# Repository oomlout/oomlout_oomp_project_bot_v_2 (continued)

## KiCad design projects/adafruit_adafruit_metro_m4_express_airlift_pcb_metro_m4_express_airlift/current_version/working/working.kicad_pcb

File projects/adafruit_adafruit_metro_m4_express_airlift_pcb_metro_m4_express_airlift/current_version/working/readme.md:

# adafruit_metro_m4_express_airlift_pcb
 
## summary 
* id: adafruit_adafruit_metro_m4_express_airlift_pcb_metro_m4_express_airlift
* user: adafruit
* name: adafruit_metro_m4_express_airlift_pcb
* board: metro_m4_express_airlift
* repo: https://github.com/adafruit/Adafruit-Metro-M4-Express-AirLift-PCB

* src_file_repo_sch: 
* src_file_repo_sch_link: https://github.com/adafruit/Adafruit-Metro-M4-Express-AirLift-PCB/tree/master/
* full details link: https://github.com/oomlout/oomlout_oomp_project_bot_v_2/tree/main/projects/adafruit_adafruit_metro_m4_express_airlift_pcb_metro_m4_express_airlift/current_version/working  

## schematic  
  
[schematic (pdf)](working_schematic.pdf) 

## pcb  

[board (pdf)](working.pdf)  

## working_bom
| Id | Designator | Footprint | Quantity | Designation | Supplier and ref |  | None | 
| --- | --- | --- | --- | --- | --- | --- | --- | 
| 1 | C7,C5 | 0603-NO | 2 | 22pF |  |  | [''] | 
| 2 | U$1 | PQFN64-1 | 1 | ATSAMD51J19 |  |  | [''] | 
| 3 | LED1 | LED3535 | 1 | WS2812B3535 |  |  | [''] | 
| 4 | @HOLE0,@HOLE1,@HOLE3,@HOLE2 |  | 4 |  |  |  | [''] | 
| 5 | C15,C8,C6,C14,C16,C4,C11,C10 | 0603-NO | 8 | .1u |  |  | [''] | 
| 6 | X5 | DCJACK_2MM_PTH | 1 | 2.1mm |  |  | [''] | 
| 7 | SW1 | SPDT_SMT_SSSS811101 | 1 |  |  |  | [''] | 
| 8 | C2 | 0805-NO | 1 | 0.1uF |  |  | [''] | 
| 9 | PC2 | PANASONIC_D | 1 | 47uF+/6.3V+ |  |  | [''] | 
| 10 | ON0 | CHIPLED_0805_NOOUTLINE | 1 | GREEN |  |  | [''] | 
| 11 | C3,C1,C20,C18,C19 | 0805-NO | 5 | 10uF |  |  | [''] | 
| 12 | SJ1 | SOLDERJUMPER_CLOSEDWIRE | 1 | AREF_3V |  |  | [''] | 
| 13 | C12,C13,C17 | 0603-NO | 3 | 0.1uF |  |  | [''] | 
| 14 | IC1 | SOT23-5L | 1 | 74AHC1G125 |  |  | [''] | 
| 15 | TR1,T2 | SOT-23 | 2 | DMP3098L-7 |  |  | [''] | 
| 16 | PC1 | PANASONIC_D | 1 | 47uF/25V |  |  | [''] | 
| 17 | FD2,FD1,FD3 | FIDUCIAL_1MM | 3 | FIDUCIAL_1MM |  |  | [''] | 
| 18 | POWER0,IOL0 | 1X08_OVALWAVE | 2 | 20610 |  |  | [''] | 
| 19 | L1 | INDUCTOR_1007 | 1 | 10uH |  |  | [''] | 
| 20 | R5,R15,R7 | 0603-NO | 3 | 10K |  |  | [''] | 
| 21 | RXLED0,TXLED0 | CHIPLED_0805_NOOUTLINE | 2 | YELLOW |  |  | [''] | 
| 22 | AD0 | 1X06_OVALWAVE | 1 | 20609 |  |  | [''] | 
| 23 | U2 | SOT23-DBV | 1 | AP2112K-3.3 |  |  | [''] | 
| 24 | X2 | 2X05_1.27MM_BOX_POSTS | 1 | 2x5 0.05 SWD" |  |  | [''] | 
| 25 | L0 | CHIPLED_0805_NOOUTLINE | 1 | RED |  |  | [''] | 
| 26 | R11 | 0603-NO | 1 | 330R |  |  | [''] | 
| 27 | U$39 | METROM4_AIRLIFT_LITE_TOP | 1 |  |  |  | [''] | 
| 28 | R1 | RESPACK_4X0603 | 1 | 100K |  |  | [''] | 
| 29 | X6 | WROOM32 | 1 | ESP32_WROOM32 |  |  | [''] | 
| 30 | IOH0 | 1X10_OVALWAVE | 1 | 20611 |  |  | [''] | 
| 31 | JP1 | 1X01_ROUND | 1 |  |  |  | [''] | 
| 32 | R10 | RESPACK_4X0603 | 1 | 10K |  |  | [''] | 
| 33 | ECC1 | SOIC8 | 1 | ATECC108 |  |  | [''] | 
| 34 | C9 | 0603-NO | 1 | 1uF |  |  | [''] | 
| 35 | D1 | SOD-123 | 1 | MBR120 |  |  | [''] | 
| 36 | ICSP0 | 2X03_ROUND_70MIL | 1 | 3x2 M |  |  | [''] | 
| 37 | X4 | XTAL3215 | 1 | 32.768 |  |  | [''] | 
| 38 | U3 | SOIC8_208MIL | 1 | GD25Q16 |  |  | [''] | 
| 39 | X3 | 4UCONN_20329_V2 | 1 | 20329 |  |  | [''] | 
| 40 | IC3 | SOT23-5 | 1 | 74LVC1G125D |  |  | [''] | 
| 41 | U1 | SOT223-R | 1 | NCP1117ST50T3G |  |  | [''] | 
| 42 | R4 | 0603-NO | 1 | 1K |  |  | [''] | 
| 43 | FB2 | 0805-NO | 1 | FERRITE |  |  | [''] | 
| 44 | RESET0 | EVQ-Q2_SMALLER | 1 | EVQQ 6mm |  |  | [''] | 
| 45 | F2 | R1206 | 1 | FUSE |  |  | [''] | 
| 46 | R2 | RESPACK_4X0603 | 1 | 1K |  |  | [''] | 
| 47 | U$27 | METROM4_AIRLIFT_LITE_BOT | 1 |  |  |  | [''] | 
| 48 | GROUND1 | SOLDERJUMPER_CLOSEDWIRE | 1 |  |  |  | [''] | 

## bom_schematic
| Ref | Qnty | Value | Cmp name | Footprint | Description | Vendor | DNP | 
| --- | --- | --- | --- | --- | --- | --- | --- | 
| AD0 | 1 | 20609 | HEADER-1X6OVALWAVE | working:1X06_OVALWAVE |  |  |  | 
| C1, C3, C18, C19, C20 | 5 | 10uF | CAP_CERAMIC0805-NOOUTLINE | working:0805-NO |  |  |  | 
| C2 | 1 | 0.1uF | CAP_CERAMIC0805-NOOUTLINE | working:0805-NO |  |  |  | 
| C4, C6, C8, C10, C11, C14, C15, C16 | 8 | .1u | CAP_CERAMIC0603_NO | working:0603-NO |  |  |  | 
| C5, C7 | 2 | 22pF | CAP_CERAMIC0603_NO | working:0603-NO |  |  |  | 
| C9 | 1 | 1uF | CAP_CERAMIC0603_NO | working:0603-NO |  |  |  | 
| C12, C13, C17 | 3 | 0.1uF | CAP_CERAMIC0603_NO | working:0603-NO |  |  |  | 
| D1 | 1 | MBR120 | DIODE-SCHOTTKYSOD-123 | working:SOD-123 |  |  |  | 
| ECC1 | 1 | ATECC108 | ATECC108 | working:SOIC8 |  |  |  | 
| F2 | 1 | FUSE | PTCFUSE-1206 | working:R1206 |  |  |  | 
| FB2 | 1 | FERRITE | FERRITE-0805NO | working:0805-NO |  |  |  | 
| FD1, FD2, FD3 | 3 | FIDUCIAL_1MM | FIDUCIAL_1MM | working:FIDUCIAL_1MM |  |  |  | 
| GROUND1 | 1 | SOLDERJUMPERCLOSED | SOLDERJUMPERCLOSED | working:SOLDERJUMPER_CLOSEDWIRE |  |  |  | 
| IC1 | 1 | 74AHC1G125 | 74AHC1G125 | working:SOT23-5L |  |  |  | 
| IC3 | 1 | 741G125DBV | 741G125DBV | working:SOT23-5 |  |  |  | 
| ICSP0 | 1 | 3x2 M | HEADER-2X3 | working:2X03_ROUND_70MIL |  |  |  | 
| IOH0 | 1 | 20611 | HEADER-1X10OVALWAVE | working:1X10_OVALWAVE |  |  |  | 
| IOL0 | 1 | 20610 | HEADER-1X8OVALWAVE | working:1X08_OVALWAVE |  |  |  | 
| JP1 | 1 | HEADER-1X1ROUND | HEADER-1X1ROUND | working:1X01_ROUND |  |  |  | 
| L0 | 1 | RED | LED0805_NOOUTLINE | working:CHIPLED_0805_NOOUTLINE |  |  |  | 
| L1 | 1 | 10uH | INDUCTOR | working:INDUCTOR_1007 |  |  |  | 
| LED1 | 1 | WS2812B3535 | WS2812B3535 | working:LED3535 |  |  |  | 
| ON0 | 1 | GREEN | LED0805_NOOUTLINE | working:CHIPLED_0805_NOOUTLINE |  |  |  | 
| PC1 | 1 | 47uF/25V | CAP_ELECTROLYTICPANASONIC_D | working:PANASONIC_D |  |  |  | 
| PC2 | 1 | 47uF+/6.3V+ | CAP_ELECTROLYTICPANASONIC_D | working:PANASONIC_D |  |  |  | 
| POWER0 | 1 | 20610 | HEADER-1X8OVALWAVE | working:1X08_OVALWAVE |  |  |  | 
| R1 | 1 | 100K | RESISTOR_4PACK | working:RESPACK_4X0603 |  |  |  | 
| R2 | 1 | 1K | RESISTOR_4PACK | working:RESPACK_4X0603 |  |  |  | 
| R4 | 1 | 1K | RESISTOR_0603_NOOUT | working:0603-NO |  |  |  | 
| R5, R7, R15 | 3 | 10K | RESISTOR_0603_NOOUT | working:0603-NO |  |  |  | 
| R10 | 1 | 10K | RESISTOR_4PACK | working:RESPACK_4X0603 |  |  |  | 
| R11 | 1 | 330R | RESISTOR_0603_NOOUT | working:0603-NO |  |  |  | 
| RESET0 | 1 | EVQQ 6mm | SWITCH_TACT_SMT_EVQQ2_SMALL | working:EVQ-Q2_SMALLER |  |  |  | 
| RXLED0 | 1 | YELLOW | LED0805_NOOUTLINE | working:CHIPLED_0805_NOOUTLINE |  |  |  | 
| SJ1 | 1 | AREF_3V | SOLDERJUMPERCLOSED | working:SOLDERJUMPER_CLOSEDWIRE |  |  |  | 
| SW1 | 1 | SWITCH_SPDT | SWITCH_SPDT | working:SPDT_SMT_SSSS811101 |  |  |  | 
| T2 | 1 | DMP3098L-7 | PMOSSOT23 | working:SOT-23 |  |  |  | 
| TR1 | 1 | DMP3098L-7 | 0297_PMV48XP | working:SOT-23 |  |  |  | 
| TXLED0 | 1 | YELLOW | LED0805_NOOUTLINE | working:CHIPLED_0805_NOOUTLINE |  |  |  | 
| U1 | 1 | NCP1117ST50T3G | LM1117SOT223-REFLOW | working:SOT223-R |  |  |  | 
| U2 | 1 | LP2985-XXDBVR | LP2985-XXDBVR | working:SOT23-DBV |  |  |  | 
| U3 | 1 | GD25Q16 | SPIFLASH_8PIN208MIL | working:SOIC8_208MIL |  |  |  | 
| U$1 | 1 | ATSAMD51J | ATSAMD51J | working:PQFN64-1 |  |  |  | 
| X2 | 1 | 2x5 0.05" SWD | JTAG-CORTEXBOXPOSTS | working:2X05_1.27MM_BOX_POSTS |  |  |  | 
| X3 | 1 | USB_W_SHIELD_V2 | USB_W_SHIELD_V2 | working:4UCONN_20329_V2 |  |  |  | 
| X4 | 1 | 32.768 | XTAL-3.2X1.5 | working:XTAL3215 |  |  |  | 
| X5 | 1 | 2.1mm | DCBARRELPTH | working:DCJACK_2MM_PTH |  |  |  | 
| X6 | 1 | ESP32_WROOM32 | ESP32_WROOM32 | working:WROOM32 |  |  |  |

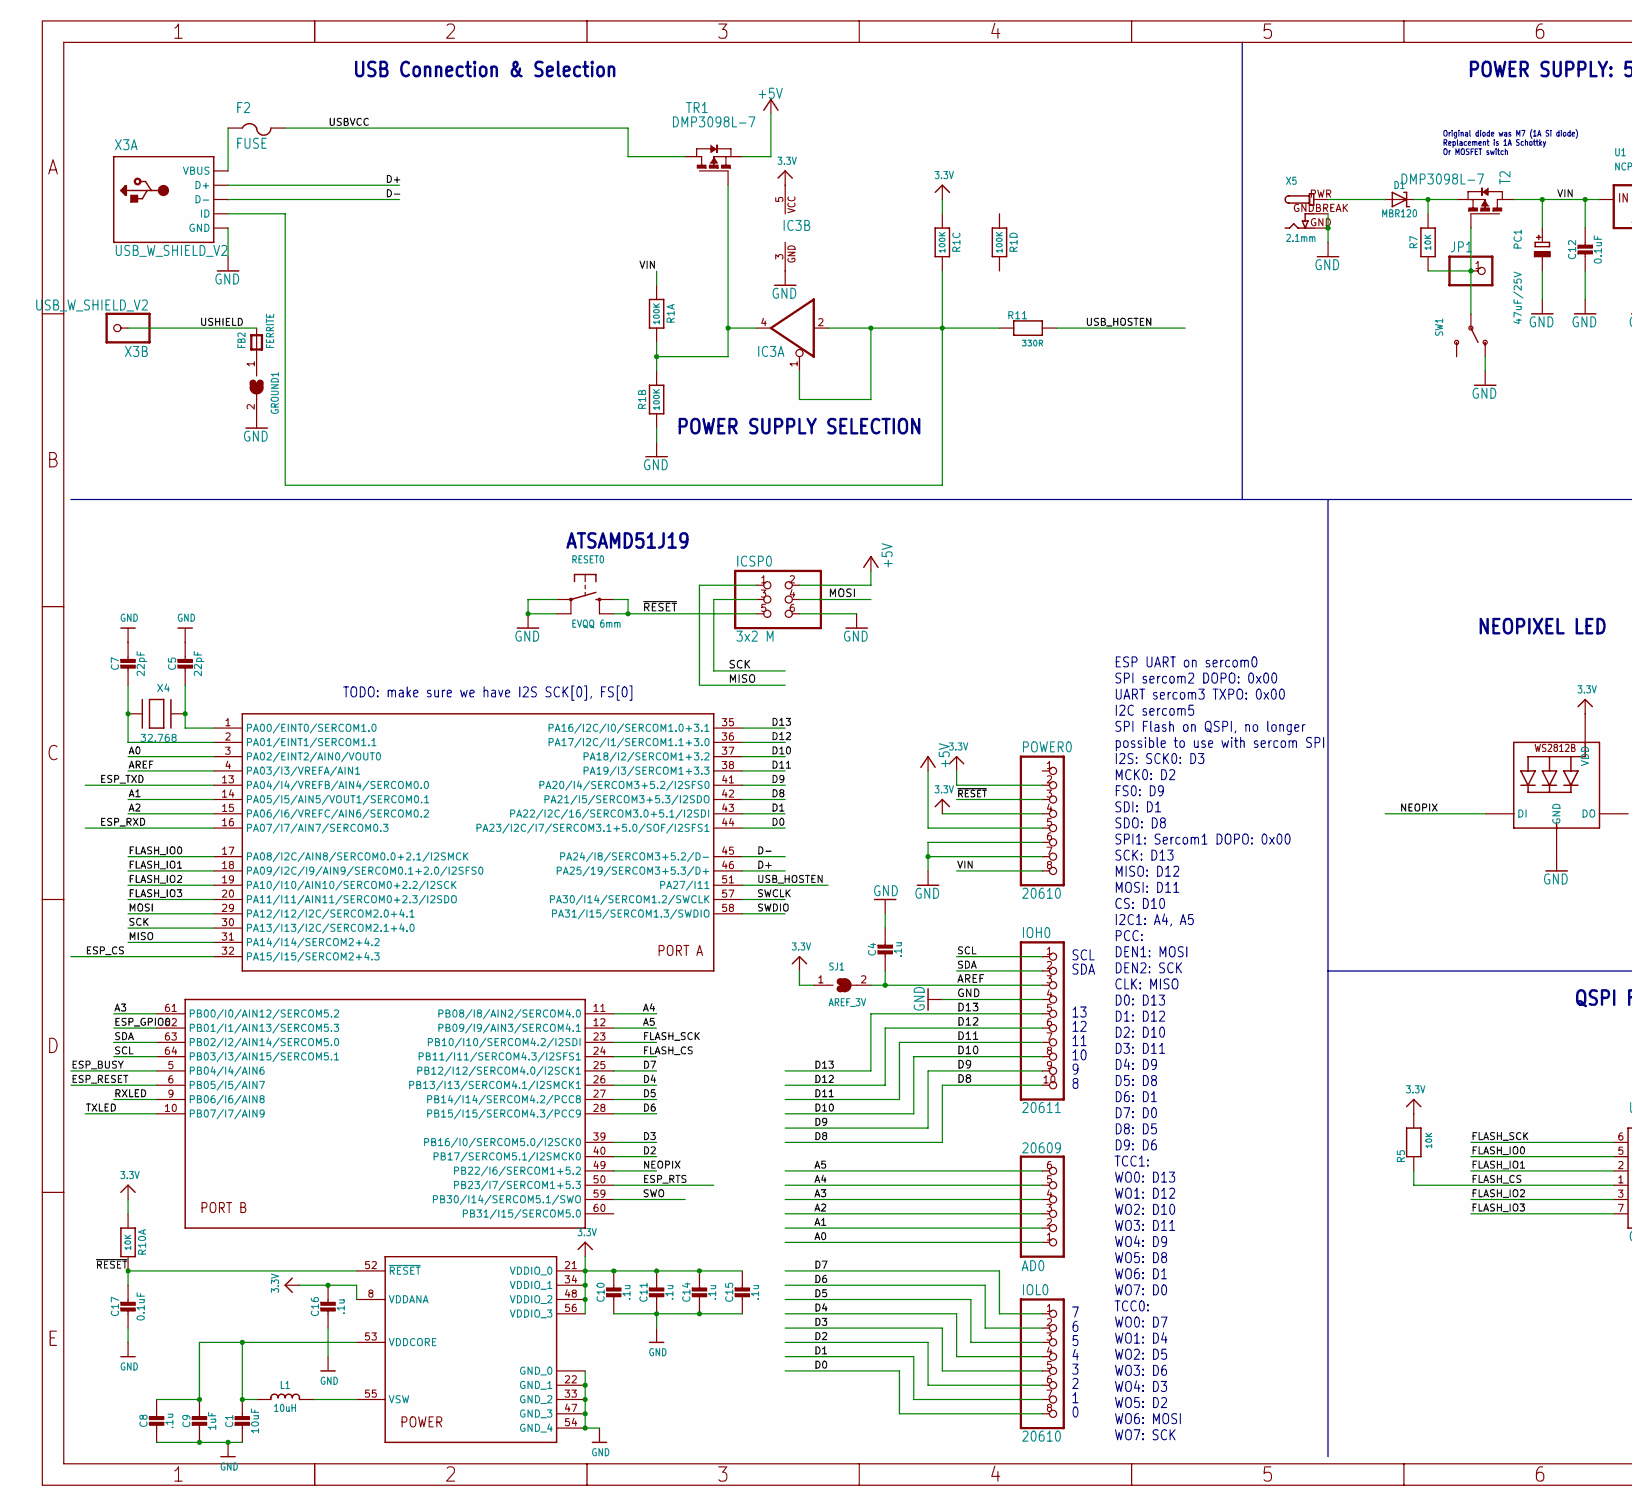
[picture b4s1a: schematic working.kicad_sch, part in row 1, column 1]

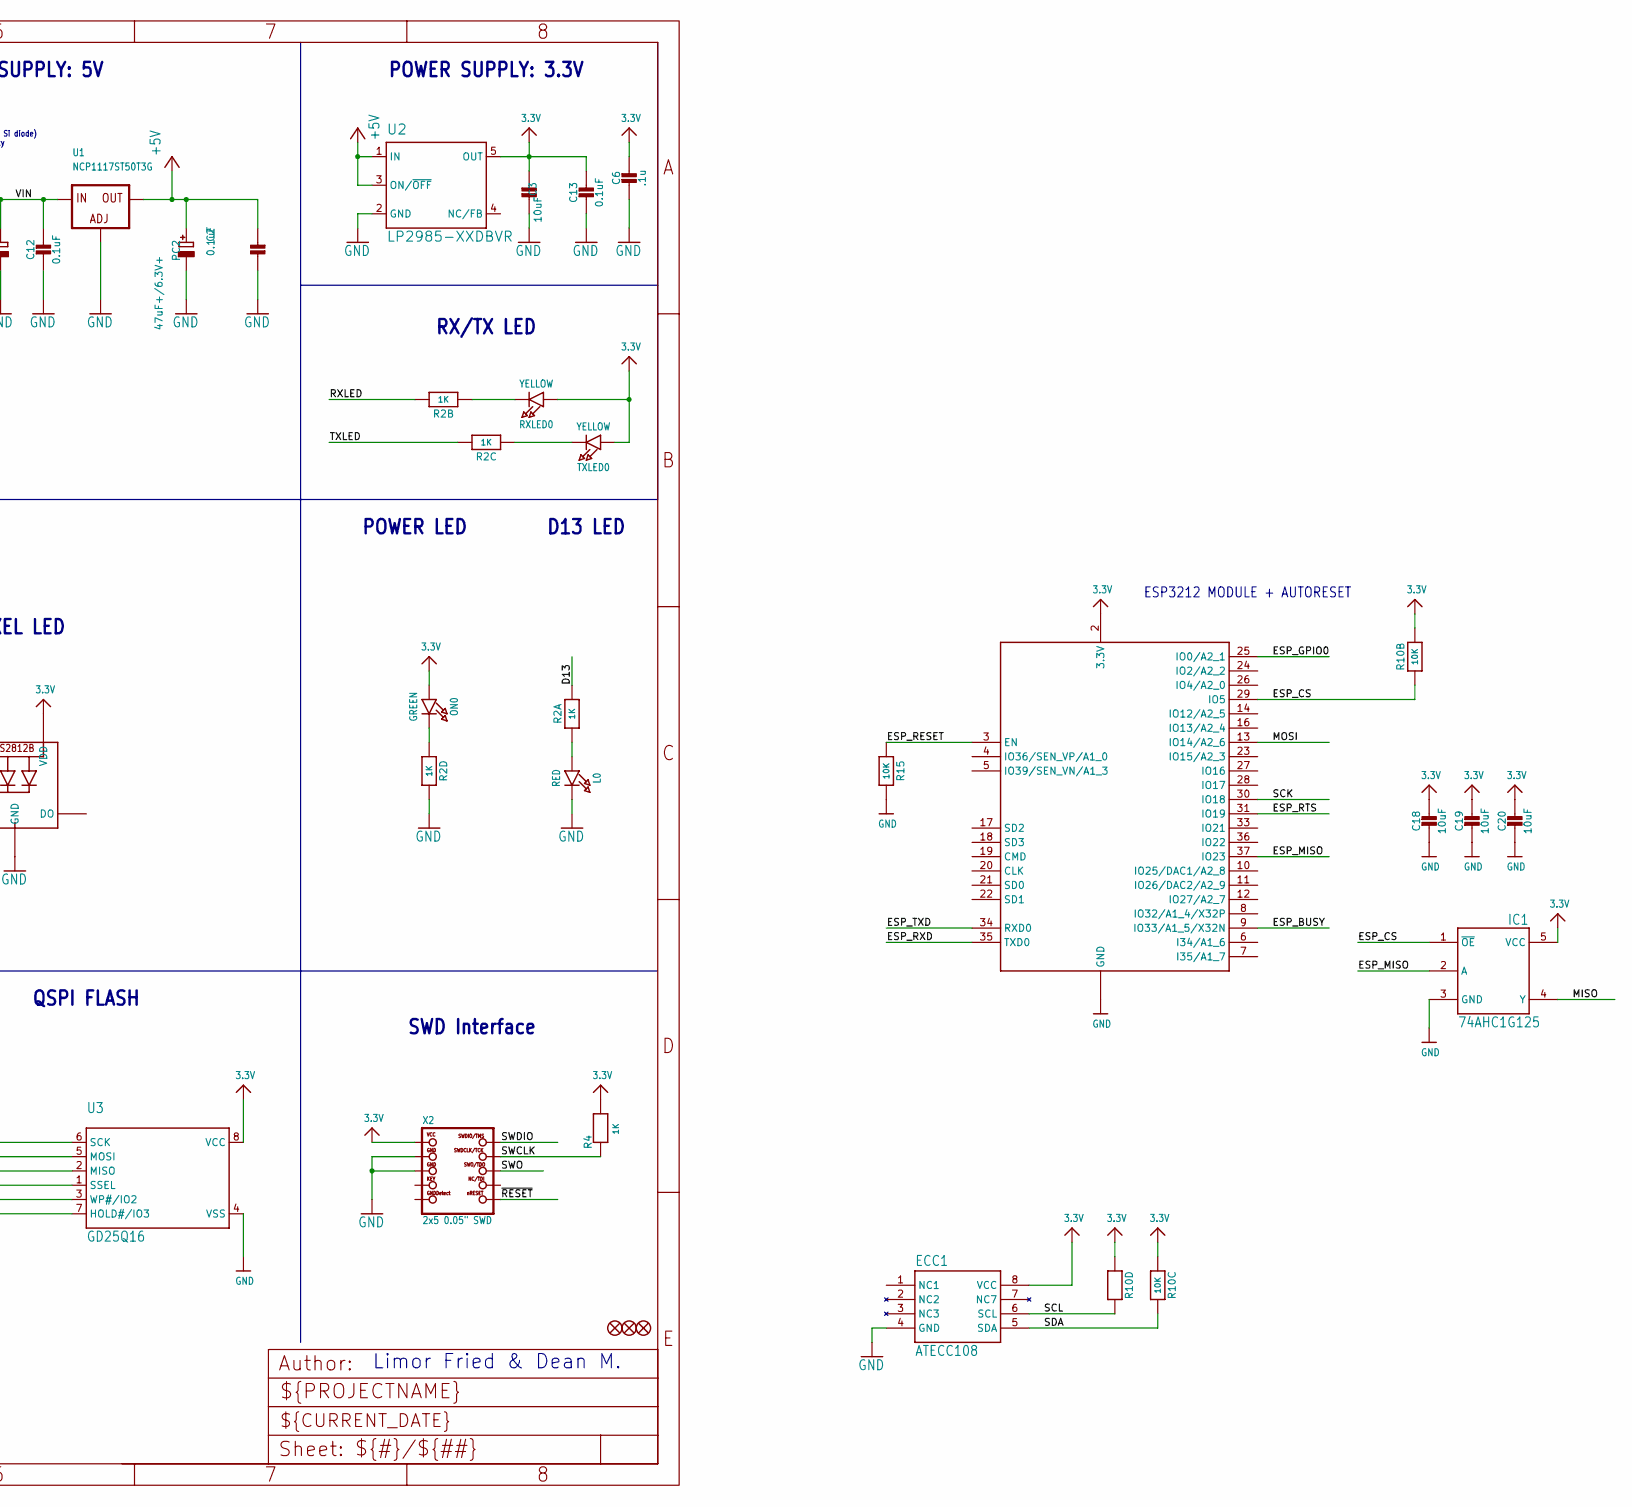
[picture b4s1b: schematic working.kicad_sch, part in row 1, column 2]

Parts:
AD0: 20609; 1X06_OVALWAVE
C1, C3, C18, C19, C20: 10uF; 0805-NO
C2: 0.1uF; 0805-NO
C4, C6, C8, C10, C11, C14, C15, C16: .1u; 0603-NO
C5, C7: 22pF; 0603-NO
C9: 1uF; 0603-NO
C12, C13, C17: 0.1uF; 0603-NO
D1: MBR120; SOD-123
ECC1: ATECC108; SOIC8
F2: FUSE; R1206
FB2: FERRITE; 0805-NO
FD1, FD2, FD3: FIDUCIAL_1MM
GROUND1: SOLDERJUMPERCLOSED; SOLDERJUMPER_CLOSEDWIRE
IC1: 74AHC1G125; SOT23-5L
IC3: 741G125DBV; SOT23-5
ICSP0: 3x2 M; 2X03_ROUND_70MIL
IOH0: 20611; 1X10_OVALWAVE
IOL0: 20610; 1X08_OVALWAVE
JP1: HEADER-1X1ROUND; 1X01_ROUND
L0: RED; CHIPLED_0805_NOOUTLINE
L1: 10uH; INDUCTOR_1007
LED1: WS2812B3535; LED3535
ON0: GREEN; CHIPLED_0805_NOOUTLINE
PC1: 47uF/25V; PANASONIC_D
PC2: 47uF+/6.3V+; PANASONIC_D
POWER0: 20610; 1X08_OVALWAVE
R1: 100K; RESPACK_4X0603
R2: 1K; RESPACK_4X0603
R4: 1K; 0603-NO
R5, R7, R15: 10K; 0603-NO
R10: 10K; RESPACK_4X0603
R11: 330R; 0603-NO
RESET0: EVQQ 6mm; EVQ-Q2_SMALLER
RXLED0: YELLOW; CHIPLED_0805_NOOUTLINE
SJ1: AREF_3V; SOLDERJUMPER_CLOSEDWIRE
SW1: SWITCH_SPDT; SPDT_SMT_SSSS811101
T2: DMP3098L-7; SOT-23
TR1: DMP3098L-7; SOT-23
TXLED0: YELLOW; CHIPLED_0805_NOOUTLINE
U1: NCP1117ST50T3G; SOT223-R
U2: LP2985-XXDBVR; SOT23-DBV
U3: GD25Q16; SOIC8_208MIL
U$1: ATSAMD51J; PQFN64-1
X2: 2x5 0.05" SWD; 2X05_1.27MM_BOX_POSTS
X3: USB_W_SHIELD_V2; 4UCONN_20329_V2
X4: 32.768; XTAL3215
X5: 2.1mm; DCJACK_2MM_PTH
X6: ESP32_WROOM32; WROOM32

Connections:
3.3V: C3.2, C6.2, C10.2, C11.2, C13.1, C14.2, C15.2, C16.2, C18.1, C19.1, C20.1, ECC1.8 (VCC), IC1.5 (VCC), IC3.5 (VCC), LED1.2 (VDD), ON0.A, POWER0.2, POWER0.4, R1.3 (1), R4.2, R5.2, R10.1, R10.3 (1), R10.4 (1), R10.7 (2), RXLED0.A, SJ1.1, TXLED0.A, U2.5 (OUT), U3.8 (VCC), U$1.8 (VDDANA), U$1.21 (VDDIO_0), U$1.34 (VDDIO_1), U$1.48 (VDDIO_2), U$1.56 (VDDIO_3), X2.1 (VCC), X6.2 (3.3V)
+5V: C2.2, ICSP0.2, PC2.+, POWER0.5, TR1.2 (S), U1.2 (OUT), U1.4 (OUT), U2.1 (IN), U2.3 (ON/~OFF)
A0: AD0.1, U$1.3 (PA02/EINT2/AIN0/VOUT0)
A1: AD0.2, U$1.14 (PA05/I5/AIN5/VOUT1/SERCOM0.1)
A2: AD0.3, U$1.15 (PA06/I6/VREFC/AIN6/SERCOM0.2)
A3: AD0.4, U$1.61 (PB00/I0/AIN12/SERCOM5.2)
A4: AD0.5, U$1.11 (PB08/I8/AIN2/SERCOM4.0)
A5: AD0.6, U$1.12 (PB09/I9/AIN3/SERCOM4.1)
AREF: C4.1, IOH0.3, SJ1.2, U$1.4 (PA03/I3/VREFA/AIN1)
D0: IOL0.8, U$1.44 (PA23/I2C/I7/SERCOM3.1+5.0/SOF/I2SFS1)
D1: IOL0.7, U$1.43 (PA22/I2C/16/SERCOM3.0+5.1/I2SDI)
D2: IOL0.6, U$1.40 (PB17/SERCOM5.1/I2SMCK0)
D3: IOL0.5, U$1.39 (PB16/I0/SERCOM5.0/I2SCK0)
D4: IOL0.4, U$1.26 (PB13/I13/SERCOM4.1/I2SMCK1)
D5: IOL0.3, U$1.27 (PB14/I14/SERCOM4.2/PCC8)
D6: IOL0.2, U$1.28 (PB15/I15/SERCOM4.3/PCC9)
D7: IOL0.1, U$1.25 (PB12/I12/SERCOM4.0/I2SCK1)
D8: IOH0.10, U$1.42 (PA21/I5/SERCOM3+5.3/I2SDO)
D9: IOH0.9, U$1.41 (PA20/I4/SERCOM3+5.2/I2SFS0)
D10: IOH0.8, U$1.37 (PA18/I2/SERCOM1+3.2)
D11: IOH0.7, U$1.38 (PA19/I3/SERCOM1+3.3)
D12: IOH0.6, U$1.36 (PA17/I2C/I1/SERCOM1.1+3.0)
D13: IOH0.5, R2.8 (2), U$1.35 (PA16/I2C/I0/SERCOM1.0+3.1)
D+: U$1.46 (PA25/19/SERCOM3+5.3/D+), X3.D+
D-: U$1.45 (PA24/I8/SERCOM3+5.2/D-), X3.D-
ESP_BUSY: U$1.5 (PB04/I4/AIN6), X6.9 (IO33/A1_5/X32N)
ESP_CS: IC1.1 (~OE), R10.2 (1), U$1.32 (PA15/I15/SERCOM2+4.3), X6.29 (IO5)
ESP_GPIO0: U$1.62 (PB01/I1/AIN13/SERCOM5.3), X6.25 (IO0/A2_1)
ESP_MISO: IC1.2 (A), X6.37 (IO23)
ESP_RESET: R15.1, U$1.6 (PB05/I5/AIN7), X6.3 (EN)
ESP_RTS: U$1.50 (PB23/I7/SERCOM1+5.3), X6.31 (IO19)
ESP_RXD: U$1.16 (PA07/I7/AIN7/SERCOM0.3), X6.35 (TXD0)
ESP_TXD: U$1.13 (PA04/I4/VREFB/AIN4/SERCOM0.0), X6.34 (RXD0)
FLASH_CS: R5.1, U3.1 (SSEL), U$1.24 (PB11/I11/SERCOM4.3/I2SFS1)
FLASH_IO0: U3.5 (MOSI), U$1.17 (PA08/I2C/AIN8/SERCOM0.0+2.1/I2SMCK)
FLASH_IO1: U3.2 (MISO), U$1.18 (PA09/I2C/I9/AIN9/SERCOM0.1+2.0/I2SFS0)
FLASH_IO2: U3.3 (WP#/IO2), U$1.19 (PA10/I10/AIN10/SERCOM0+2.2/I2SCK)
FLASH_IO3: U3.7 (HOLD#/IO3), U$1.20 (PA11/I11/AIN11/SERCOM0+2.3/I2SDO)
FLASH_SCK: U3.6 (SCK), U$1.23 (PB10/I10/SERCOM4.2/I2SDI)
GND: C1.2, C2.1, C3.1, C4.2, C5.2, C6.1, C7.2, C8.1, C9.2, C10.1, C11.1, C12.2, C13.2, C14.1, C15.1, C16.1, C17.1, C18.2, C19.2, C20.2, ECC1.4 (GND), GROUND1.2, IC1.3 (GND), IC3.3 (GND), ICSP0.6, IOH0.4, L0.C, LED1.4 (GND), PC1.-, PC2.-, POWER0.6, POWER0.7, R1.2 (1), R2.5 (2), R15.2, RESET0.A, RESET0.A' (P1), SW1.A (O), U1.1 (ADJ), U2.2 (GND), U3.4 (VSS), U$1.7 (GND_0), U$1.22 (GND_1), U$1.33 (GND_2), U$1.47 (GND_3), U$1.54 (GND_4), U$1.EXP (GND_0), X2.3 (GND@1), X2.5 (GND@2), X3.GND, X5.GND, X5.GNDBREAK, X6.1 (GND), X6.15 (GND), X6.38 (GND), X6.P$1 (GND)
MISO: IC1.4 (Y), ICSP0.1, U$1.31 (PA14/I14/SERCOM2+4.2)
MOSI: ICSP0.4, U$1.29 (PA12/I12/I2C/SERCOM2.0+4.1), X6.13 (IO14/A2_6)
unnamed: L0.A, R2.1
unnamed: FB2.1, GROUND1.1
unnamed: ON0.C, R2.4 (1)
unnamed: L1.P$2 (2), U$1.55 (VSW)
unnamed: R2.2 (1), RXLED0.C
unnamed: R2.3 (1), TXLED0.C
unnamed: C5.1, U$1.1 (PA00/EINT0/SERCOM1.0), X4.P$1
unnamed: IC3.1 (OE), IC3.2 (I), R1.6 (2), R11.1, X3.ID
unnamed: IC3.4 (O), R1.7 (2), R1.8 (2), TR1.3 (G)
unnamed: C7.1, U$1.2 (PA01/EINT1/SERCOM1.1), X4.P$2
unnamed: D1.C, R7.2, T2.2 (S)
NEOPIX: LED1.1 (DI), U$1.49 (PB22/I6/SERCOM1+5.2)
PWRIN: D1.A, X5.PWR
PWR_SWITCH: JP1.1, R7.1, SW1.B, T2.3 (G)
RXLED: R2.7 (2), U$1.9 (PB06/I6/AIN8)
SCK: ICSP0.3, U$1.30 (PA13/I13/I2C/SERCOM2.1+4.0), X6.30 (IO18)
SCL: ECC1.6 (SCL), IOH0.1, R10.5 (2), U$1.64 (PB03/I3/AIN15/SERCOM5.1)
SDA: ECC1.5 (SDA), IOH0.2, R10.6 (2), U$1.63 (PB02/I2/AIN14/SERCOM5.0)
SWCLK: R4.1, U$1.57 (PA30/I14/SERCOM1.2/SWCLK), X2.4 (SWDCLK)
SWDIO: U$1.58 (PA31/I15/SERCOM1.3/SWDIO), X2.2 (SWDIO)
SWO: U$1.59 (PB30/I14/SERCOM5.1/SWO), X2.6 (SWO)
TXLED: R2.6 (2), U$1.10 (PB07/I7/AIN9)
USBVCC: F2.2, TR1.1 (D)
USB_HOSTEN: R11.2, U$1.51 (PA27/I11)
USHIELD: FB2.2, X3.BASE@1 (1), X3.BASE@2 (1), X3.SPRT@1 (1), X3.SPRT@2 (1), X3.SPRT@3 (1), X3.SPRT@4 (1)
VBUS: F2.1, X3.VBUS
VDDCORE: C1.1, C8.2, C9.1, L1.P$1 (1), U$1.53 (VDDCORE)
VIN: C12.1, PC1.+, POWER0.8, R1.1, T2.1 (D), U1.3 (IN)
~RESET: C17.2, ICSP0.5, POWER0.3, R10.8 (2), RESET0.B (S), RESET0.B' (S1), U$1.52 (~RESET), X2.10 (NRESET)

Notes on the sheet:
NEOPIXEL LED
ESP UART on sercom0 SPI sercom2 DOPO: 0x00 UART sercom3 TXPO: 0x00 I2C sercom5 SPI Flash on QSPI, no longer possible to use with sercom SPI I2S: SCK0: D3 MCK0: D2 FS0: D9 SDI: D1 SDO: D8 SPI1: Sercom1 DOPO: 0x00 SCK: D13 MISO: D12 MOSI: D11 CS: D10 I2C1: A4, A5 PCC: DEN1: MOSI DEN2: SCK CLK: MISO D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
RX/TX LED
SDA
USB Connection & Selection
D13 LED
TODO: make sure we have I2S SCK[0], FS[0]
Original diode was M7 (1A Si diode) Replacement is 1A Schottky Or MOSFET switch
SCL
POWER SUPPLY SELECTION
POWER SUPPLY: 3.3V
ESP3212 MODULE + AUTORESET
SWD Interface
ATSAMD51J19
Limor Fried & Dean M.
QSPI FLASH
POWER LED
POWER SUPPLY: 5V

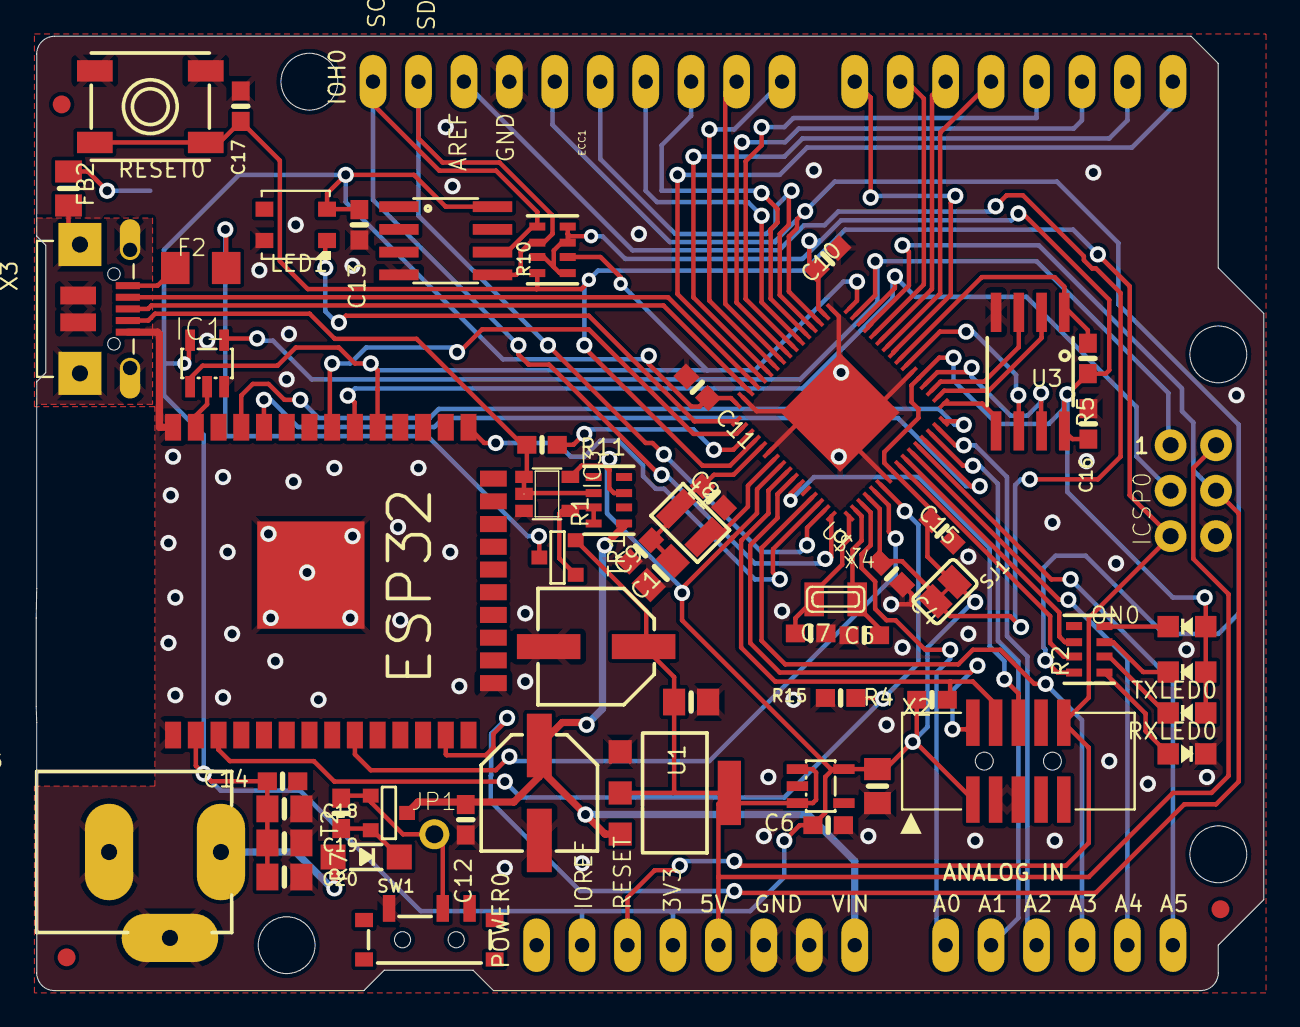
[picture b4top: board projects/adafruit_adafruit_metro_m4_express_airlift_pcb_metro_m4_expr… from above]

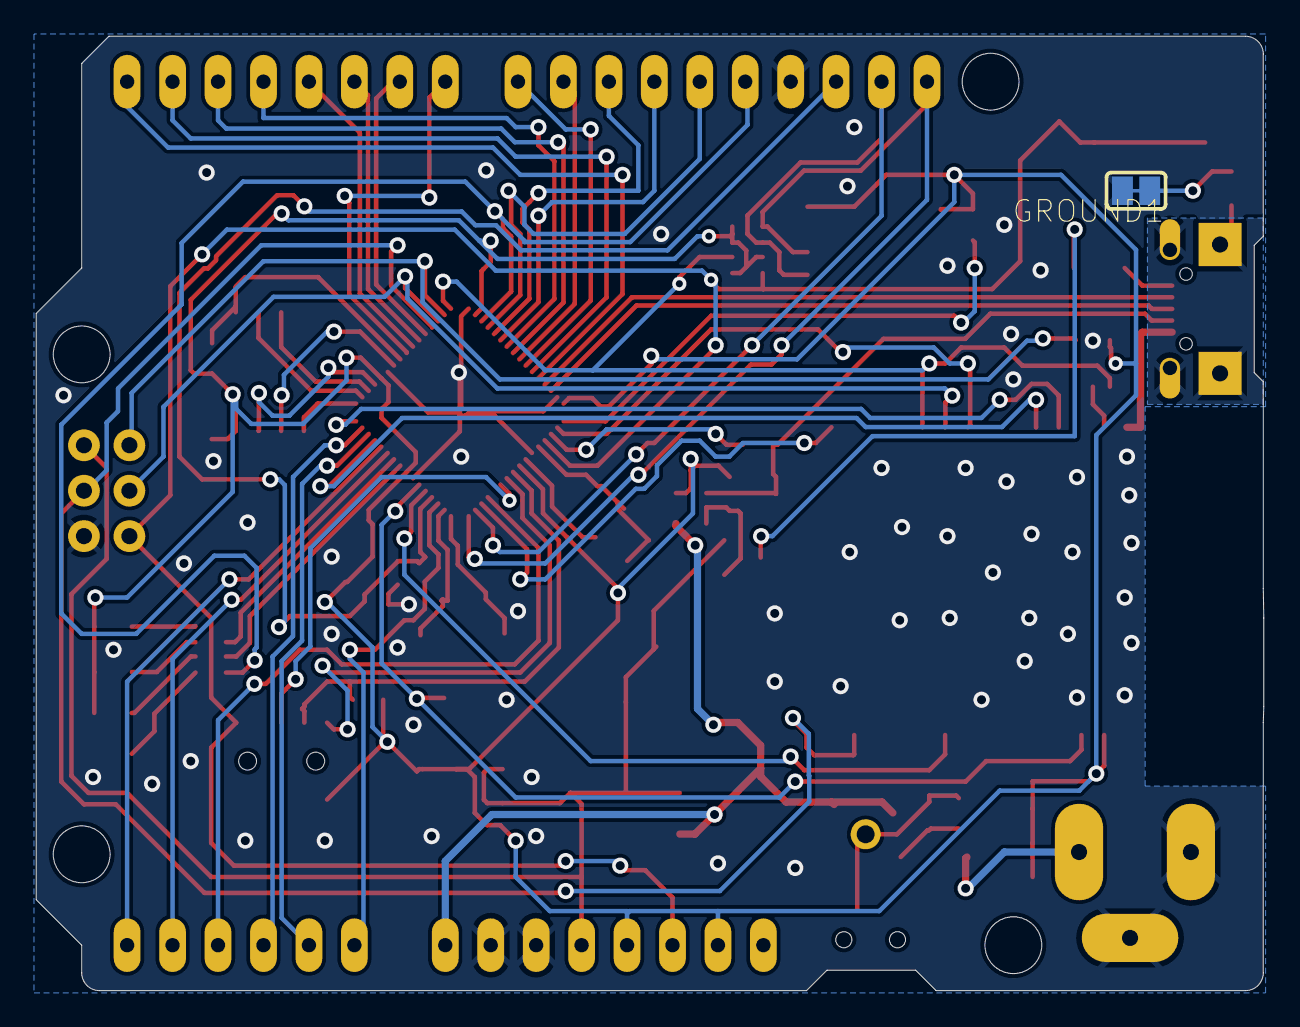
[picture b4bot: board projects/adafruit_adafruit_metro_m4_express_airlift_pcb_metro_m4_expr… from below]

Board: 2 copper layers, 68.6 x 53.3 mm, 72 parts (2 on the bottom side), 71 nets.

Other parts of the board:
@HOLE0, @HOLE1, @HOLE2, @HOLE3: (no value)
U$27: METROM4_AIRLIFT_LITE_BOT
U$39: METROM4_AIRLIFT_LITE_TOP

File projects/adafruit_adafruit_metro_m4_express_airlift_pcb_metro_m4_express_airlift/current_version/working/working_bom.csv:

"Id";"Designator";"Footprint";"Quantity";"Designation";"Supplier and ref";
1;"C7,C5";"0603-NO";2;"22pF";;;
2;"U$1";"PQFN64-1";1;"ATSAMD51J19";;;
3;"LED1";"LED3535";1;"WS2812B3535";;;
4;"@HOLE0,@HOLE1,@HOLE3,@HOLE2";"";4;"";;;
5;"C15,C8,C6,C14,C16,C4,C11,C10";"0603-NO";8;".1u";;;
6;"X5";"DCJACK_2MM_PTH";1;"2.1mm";;;
7;"SW1";"SPDT_SMT_SSSS811101";1;"";;;
8;"C2";"0805-NO";1;"0.1uF";;;
9;"PC2";"PANASONIC_D";1;"47uF+/6.3V+";;;
10;"ON0";"CHIPLED_0805_NOOUTLINE";1;"GREEN";;;
11;"C3,C1,C20,C18,C19";"0805-NO";5;"10uF";;;
12;"SJ1";"SOLDERJUMPER_CLOSEDWIRE";1;"AREF_3V";;;
13;"C12,C13,C17";"0603-NO";3;"0.1uF";;;
14;"IC1";"SOT23-5L";1;"74AHC1G125";;;
15;"TR1,T2";"SOT-23";2;"DMP3098L-7";;;
16;"PC1";"PANASONIC_D";1;"47uF/25V";;;
17;"FD2,FD1,FD3";"FIDUCIAL_1MM";3;"FIDUCIAL_1MM";;;
18;"POWER0,IOL0";"1X08_OVALWAVE";2;"20610";;;
19;"L1";"INDUCTOR_1007";1;"10uH";;;
20;"R5,R15,R7";"0603-NO";3;"10K";;;
21;"RXLED0,TXLED0";"CHIPLED_0805_NOOUTLINE";2;"YELLOW";;;
22;"AD0";"1X06_OVALWAVE";1;"20609";;;
23;"U2";"SOT23-DBV";1;"AP2112K-3.3";;;
24;"X2";"2X05_1.27MM_BOX_POSTS";1;"2x5 0.05" SWD";;;
25;"L0";"CHIPLED_0805_NOOUTLINE";1;"RED";;;
26;"R11";"0603-NO";1;"330R";;;
27;"U$39";"METROM4_AIRLIFT_LITE_TOP";1;"";;;
28;"R1";"RESPACK_4X0603";1;"100K";;;
29;"X6";"WROOM32";1;"ESP32_WROOM32";;;
30;"IOH0";"1X10_OVALWAVE";1;"20611";;;
31;"JP1";"1X01_ROUND";1;"";;;
32;"R10";"RESPACK_4X0603";1;"10K";;;
33;"ECC1";"SOIC8";1;"ATECC108";;;
34;"C9";"0603-NO";1;"1uF";;;
35;"D1";"SOD-123";1;"MBR120";;;
36;"ICSP0";"2X03_ROUND_70MIL";1;"3x2 M";;;
37;"X4";"XTAL3215";1;"32.768";;;
38;"U3";"SOIC8_208MIL";1;"GD25Q16";;;
39;"X3";"4UCONN_20329_V2";1;"20329";;;
40;"IC3";"SOT23-5";1;"74LVC1G125D";;;
41;"U1";"SOT223-R";1;"NCP1117ST50T3G";;;
42;"R4";"0603-NO";1;"1K";;;
43;"FB2";"0805-NO";1;"FERRITE";;;
44;"RESET0";"EVQ-Q2_SMALLER";1;"EVQQ 6mm";;;
45;"F2";"R1206";1;"FUSE";;;
46;"R2";"RESPACK_4X0603";1;"1K";;;
47;"U$27";"METROM4_AIRLIFT_LITE_BOT";1;"";;;
48;"GROUND1";"SOLDERJUMPER_CLOSEDWIRE";1;"";;;
